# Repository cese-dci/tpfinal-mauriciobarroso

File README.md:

# EEMON - Energy Meter Monitor

El sistema propuesto se encarga de obtener los pulsos ópticos provenientes de un medidor de energía eléctrica docmiciliario, los almacena en una memoria no volátil para procesarlos y enviarlos a un gateway LoRaWAN propiedad de la empresa prestadora del servicio.

También, posee la capacidad de conectarse a una red Wi-Fi o generar una propia y funcionar como servidor web para que el abonado del servicio eléctrico pueda acceder a una interfaz desde donde podrá observar su consumo de energía eléctrica actual y un historial del mismo.

El PCB diseñado tendrá la función de servir como soporte a todos los componentes del sistema que dejarán de ser placas de desarrollo y serán reemplazados por componentes sueltos, también se servirá como soporte para la instalación de conectores apropiados para los módulos de conversión óptico-eléctrico y el programador del microcontrolador.

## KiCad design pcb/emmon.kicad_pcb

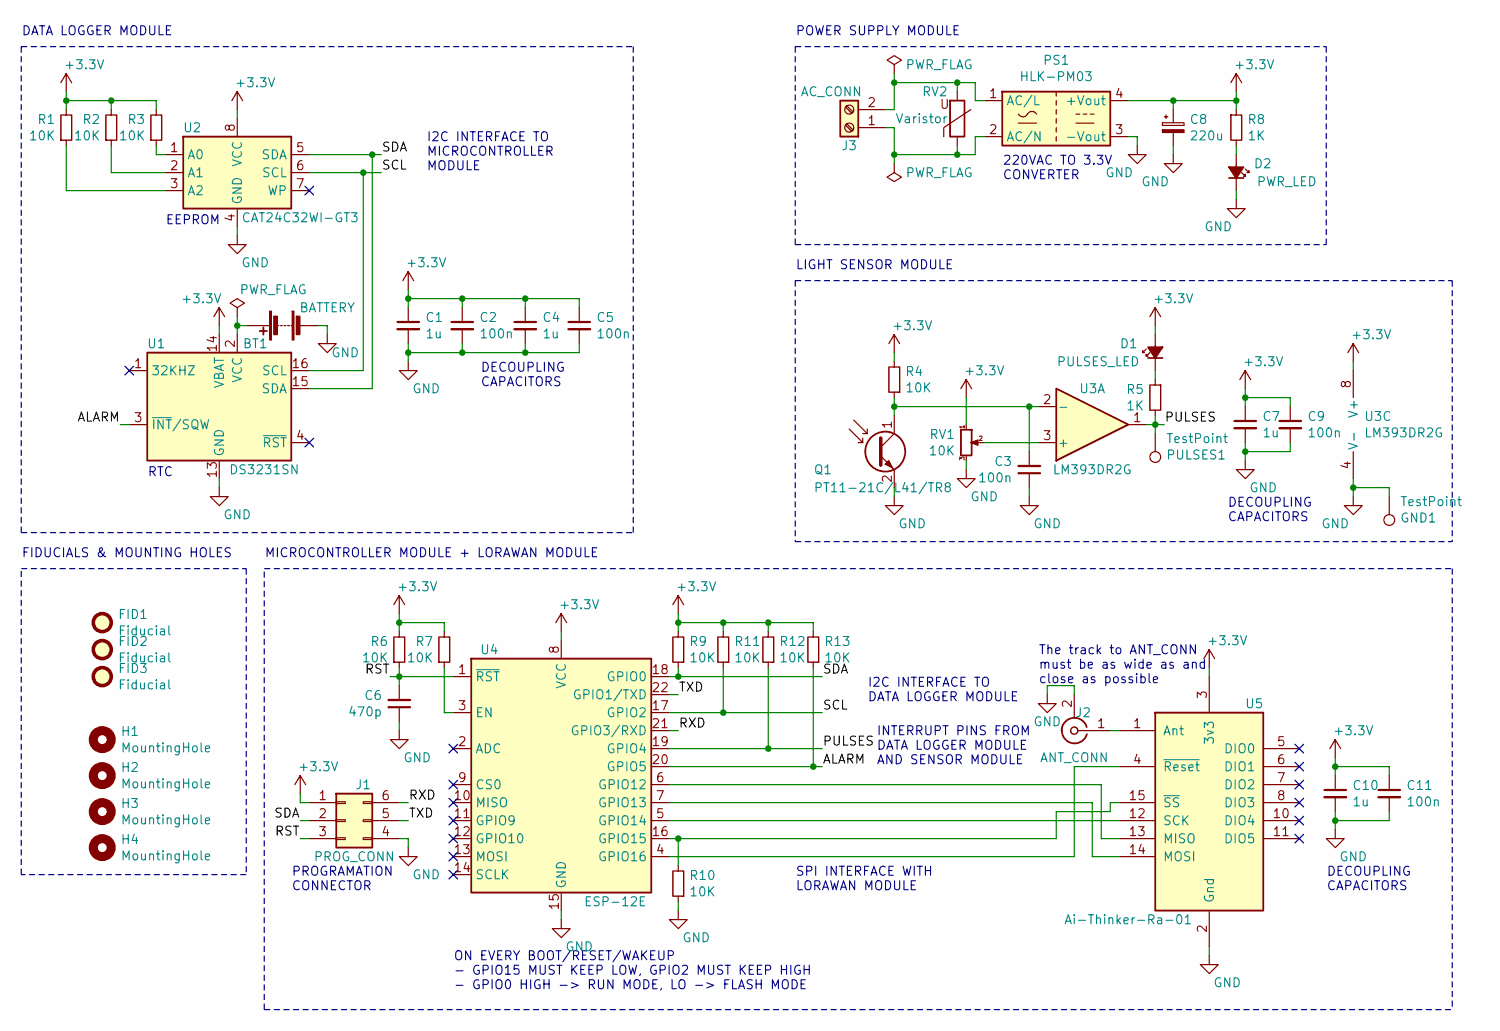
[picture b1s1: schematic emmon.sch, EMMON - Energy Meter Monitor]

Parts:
BT1: BATTERY; BatteryHolder_Keystone_1060_1x2032; LCSC C70377
C1, C4, C7, C10: 1u; C_0805_2012Metric_Pad1.15x1.40mm_HandSolder; LCSC C28323
C2, C5, C9, C11: 100n; C_0805_2012Metric_Pad1.15x1.40mm_HandSolder; LCSC C49678
C3: 100n; C_0805_2012Metric_Pad1.15x1.40mm_HandSolder
C6: 470p; C_0805_2012Metric_Pad1.15x1.40mm_HandSolder; LCSC C1743
C8: 220u; C_Radial_D6.3mm_H11.0mm_P2.50mm; LCSC C271304
D1: PULSES_LED; LED_D3.0mm
D2: PWR_LED; LED_D3.0mm
FID1, FID2, FID3: Fiducial; Fiducial_1mm_Mask2mm
GND1: TestPoint; TestPoint_THTPad_3.0x3.0mm_Drill1.5mm
H1, H2, H3, H4: MountingHole; MountingHole_2.7mm_M2.5
J1: PROG_CONN; PinHeader_2x03_P2.54mm_Vertical; LCSC C65114
J2: ANT_CONN; SMA_Molex_73251-1153_EdgeMount_Horizontal; LCSC C496550
J3: AC_CONN; TerminalBlock_Phoenix_MKDS-1,5-2-5.08_1x02_P5.08mm_Horizont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; LCSC C89120
PS1: HLK-PM03; Converter_ACDC_HiLink_HLK-PMxx; LCSC C209904
PULSES1: TestPoint; TestPoint_THTPad_3.0x3.0mm_Drill1.5mm
Q1: PT11-21C/L41/TR8; LED_1206_3216Metric_Pad1.42x1.75mm_HandSolder; LCSC C16746
R1, R2, R3, R4, R6, R7, R9, R10, R11, R12, R13: 10K; R_0805_2012Metric_Pad1.15x1.40mm_HandSolder; LCSC C17414
R5, R8: 1K; R_0805_2012Metric_Pad1.15x1.40mm_HandSolder; LCSC C17513
RV1: 10K; Potentiometer_Bourns_3386P_Vertical; LCSC C118953
RV2: Varistor; RV_Disc_D12mm_W3.9mm_P7.5mm; LCSC C233178
U1: DS3231SN; SOIC-16W_7.5x10.3mm_P1.27mm; LCSC C9866
U2: CAT24C32WI-GT3; SOIC-8_3.9x4.9mm_P1.27mm; LCSC C81193
U3: LM393DR2G; SOIC-8_3.9x4.9mm_P1.27mm; LCSC C7955
U4: ESP-12E; LCSC C89297
U5: Ai-Thinker-Ra-01; Ai-Thinker-Ra-01-LoRa; LCSC C90040

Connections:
+3V3: C1.1, C2.1, C4.1, C5.1, C7.1, C8.1, C9.1, C10.1, C11.1, D1.2 (A), J1.1, PS1.4 (+Vout), R1.2, R2.2, R3.2, R4.2, R6.2, R7.2, R8.1, R9.2, R11.2, R12.2, R13.2, RV1.1, U1.14 (VBAT), U2.8 (VCC), U3.8 (V+), U4.8 (VCC), U5.3 (3v3)
/ALARM: R13.1, U1.3 (~INT~/SQW), U4.20 (GPIO5)
/PULSES: PULSES1.1, R5.2, R12.1, U3.1, U4.19 (GPIO4)
/RST: C6.2, J1.3, R6.1, U4.1 (~RST)
/RXD: J1.6, U4.21 (GPIO3/RXD)
/SCL: R11.1, U1.16 (SCL), U2.6 (SCL), U4.17 (GPIO2)
/SDA: J1.2, R9.1, U1.15 (SDA), U2.5 (SDA), U4.18 (GPIO0)
/TXD: J1.5, U4.22 (GPIO1/TXD)
GND: BT1.2 (-), C1.2, C2.2, C3.1, C4.2, C5.2, C6.1, C7.2, C8.2, C9.2, C10.2, C11.2, D2.1 (K), GND1.1, J1.4, J2.2 (Ext), PS1.3 (-Vout), Q1.2 (E), R10.1, RV1.3, U1.5 (GND), U1.6 (GND), U1.7 (GND), U1.8 (GND), U1.9 (GND), U1.10 (GND), U1.11 (GND), U1.12 (GND), U1.13 (GND), U2.4 (GND), U3.4 (V-), U4.15 (GND), U5.2 (Gnd), U5.9 (Gnd), U5.16 (Gnd)
unnamed: BT1.1 (+), U1.2 (VCC)
unnamed: C3.2, Q1.1 (C), R4.1, U3.2 (-)
unnamed: D1.1 (K), R5.1
unnamed: D2.2 (A), R8.2
unnamed: J2.1 (In), U5.1 (Ant)
unnamed: J3.1, PS1.2 (AC/N), RV2.1
unnamed: J3.2, PS1.1 (AC/L), RV2.2
unnamed: R1.1, U2.3 (A2)
unnamed: R2.1, U2.2 (A1)
unnamed: R3.1, U2.1 (A0)
unnamed: R7.1, U4.3 (EN)
unnamed: R10.2, U4.16 (GPIO15), U5.15 (~SS)
unnamed: RV1.2, U3.3 (+)
unnamed: U4.4 (GPIO16), U5.4 (~Reset)
unnamed: U4.5 (GPIO14), U5.12 (SCK)
unnamed: U4.6 (GPIO12), U5.13 (MISO)
unnamed: U4.7 (GPIO13), U5.14 (MOSI)

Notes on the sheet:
LIGHT SENSOR MODULE
DECOUPLING CAPACITORS
EEPROM
RTC
DATA LOGGER MODULE
FIDUCIALS & MOUNTING HOLES
POWER SUPPLY MODULE
I2C INTERFACE TO MICROCONTROLLER MODULE
I2C INTERFACE TO DATA LOGGER MODULE
INTERRUPT PINS FROM DATA LOGGER MODULE AND SENSOR MODULE
220VAC TO 3.3V CONVERTER
MICROCONTROLLER MODULE + LORAWAN MODULE
SPI INTERFACE WITH LORAWAN MODULE
ON EVERY BOOT/RESET/WAKEUP - GPIO15 MUST KEEP LOW, GPIO2 MUST KEEP HIGH - GPIO0 HIGH -> RUN MODE, LO -> FLASH MODE
PROGRAMATION CONNECTOR
The track to ANT_CONN must be as wide as and close as possible

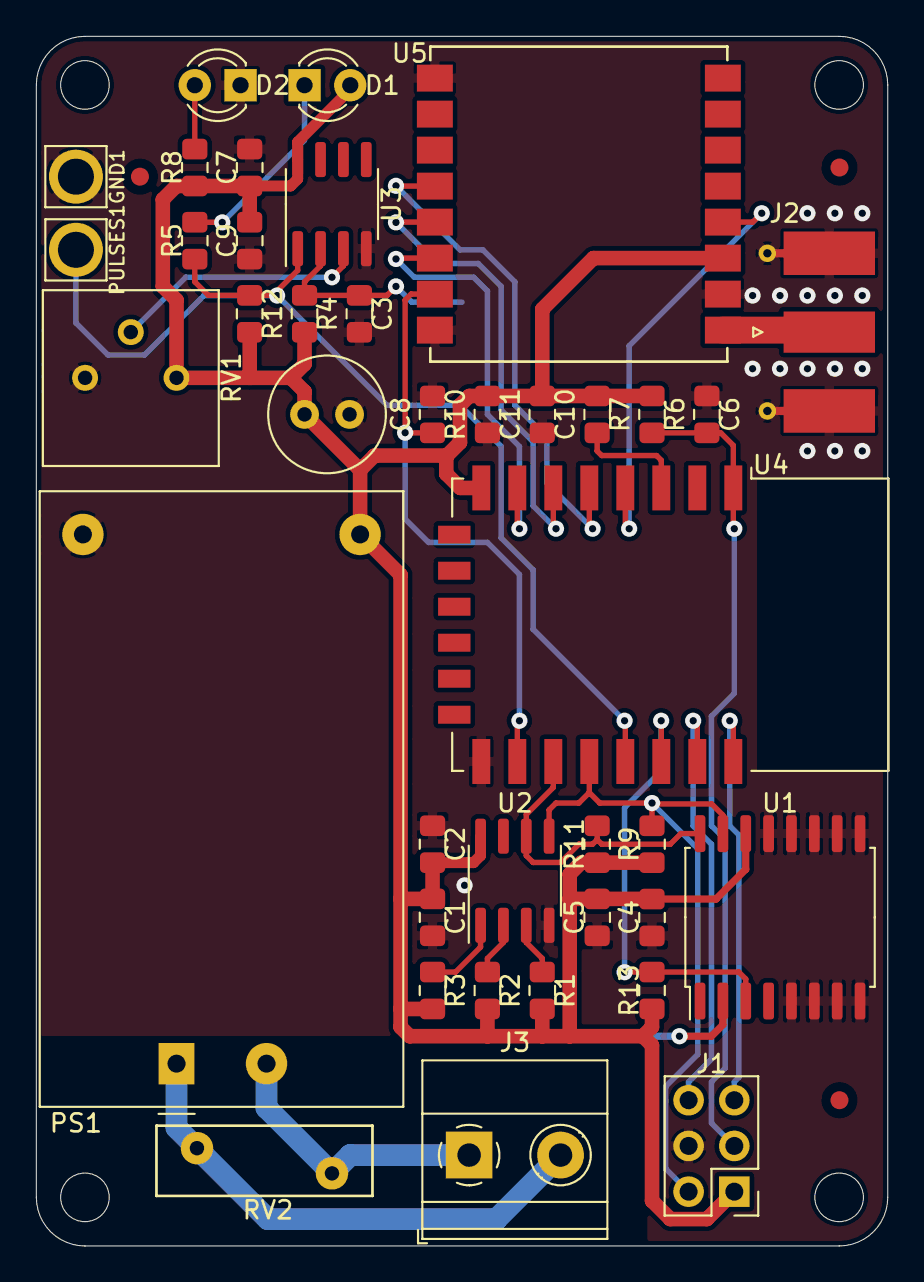
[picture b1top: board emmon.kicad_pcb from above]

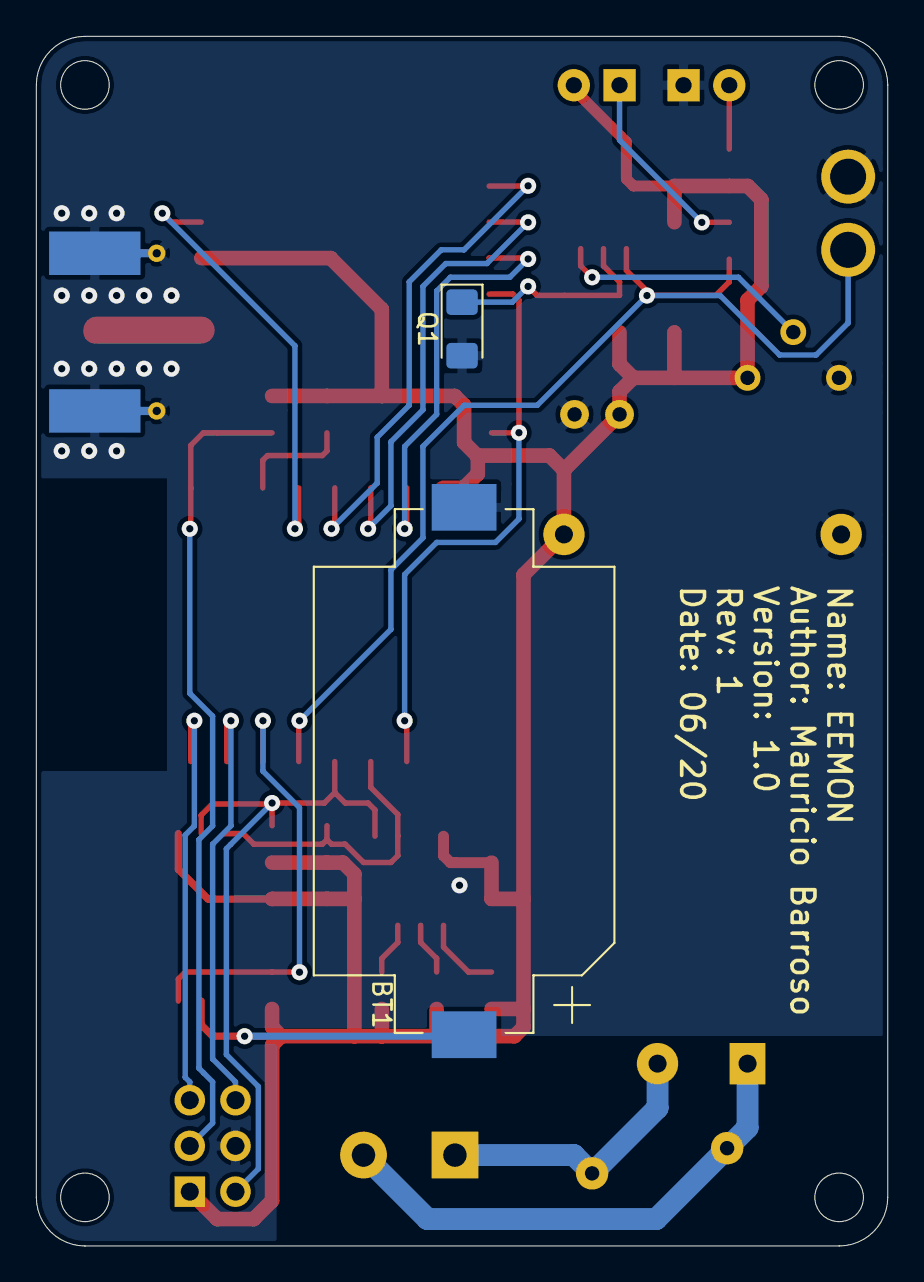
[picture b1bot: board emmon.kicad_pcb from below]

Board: 2 copper layers, 47.3 x 67.2 mm, 48 parts (2 on the bottom side), 26 nets.

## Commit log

2020-05-09 se agregan datasheets y el proyecto de kicad
2020-05-17 se avanza en el ruteo de pistas
2020-06-06 se agregan modelos 3D
2020-06-06 se completa el esquemático y se avanza en el posicionamiento del pcb
2020-06-06 se elimina carpeta gerber
2020-06-06 se eliminan archivos temporales
2020-06-06 se eliminan archivos temporales y de backup
2020-06-06 se agrega modelo 3D para RA-01
2020-06-12 se edita el esquemático y se añade el pcb
2020-06-12 se cambia la ubicación de los modelos 3d
2020-06-12 se modifican los anchos de pista del pcb
2020-06-19 Se corrigen las observaciones del docente
2020-06-19 se agregan datasheets de los componentes principales
2020-06-19 se agrega texto informativo en la sergrafía
2020-06-19 se cambia la ruta de los componentes 3D
2020-06-20 se agrega información del sistema a implementar
2020-06-20 se ejecuta el DRC cambiando el ancho de pista
2020-06-20 se cambia la posición de los capacitores de bypass de U5
2020-06-20 se agrega licencia
2020-06-20 se corrige linea de AC
2020-07-03 se aplican las correciones de la revisión del profesor

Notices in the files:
pcb/emmon.kicad_pcb:
Licencia CC BY 4.0
